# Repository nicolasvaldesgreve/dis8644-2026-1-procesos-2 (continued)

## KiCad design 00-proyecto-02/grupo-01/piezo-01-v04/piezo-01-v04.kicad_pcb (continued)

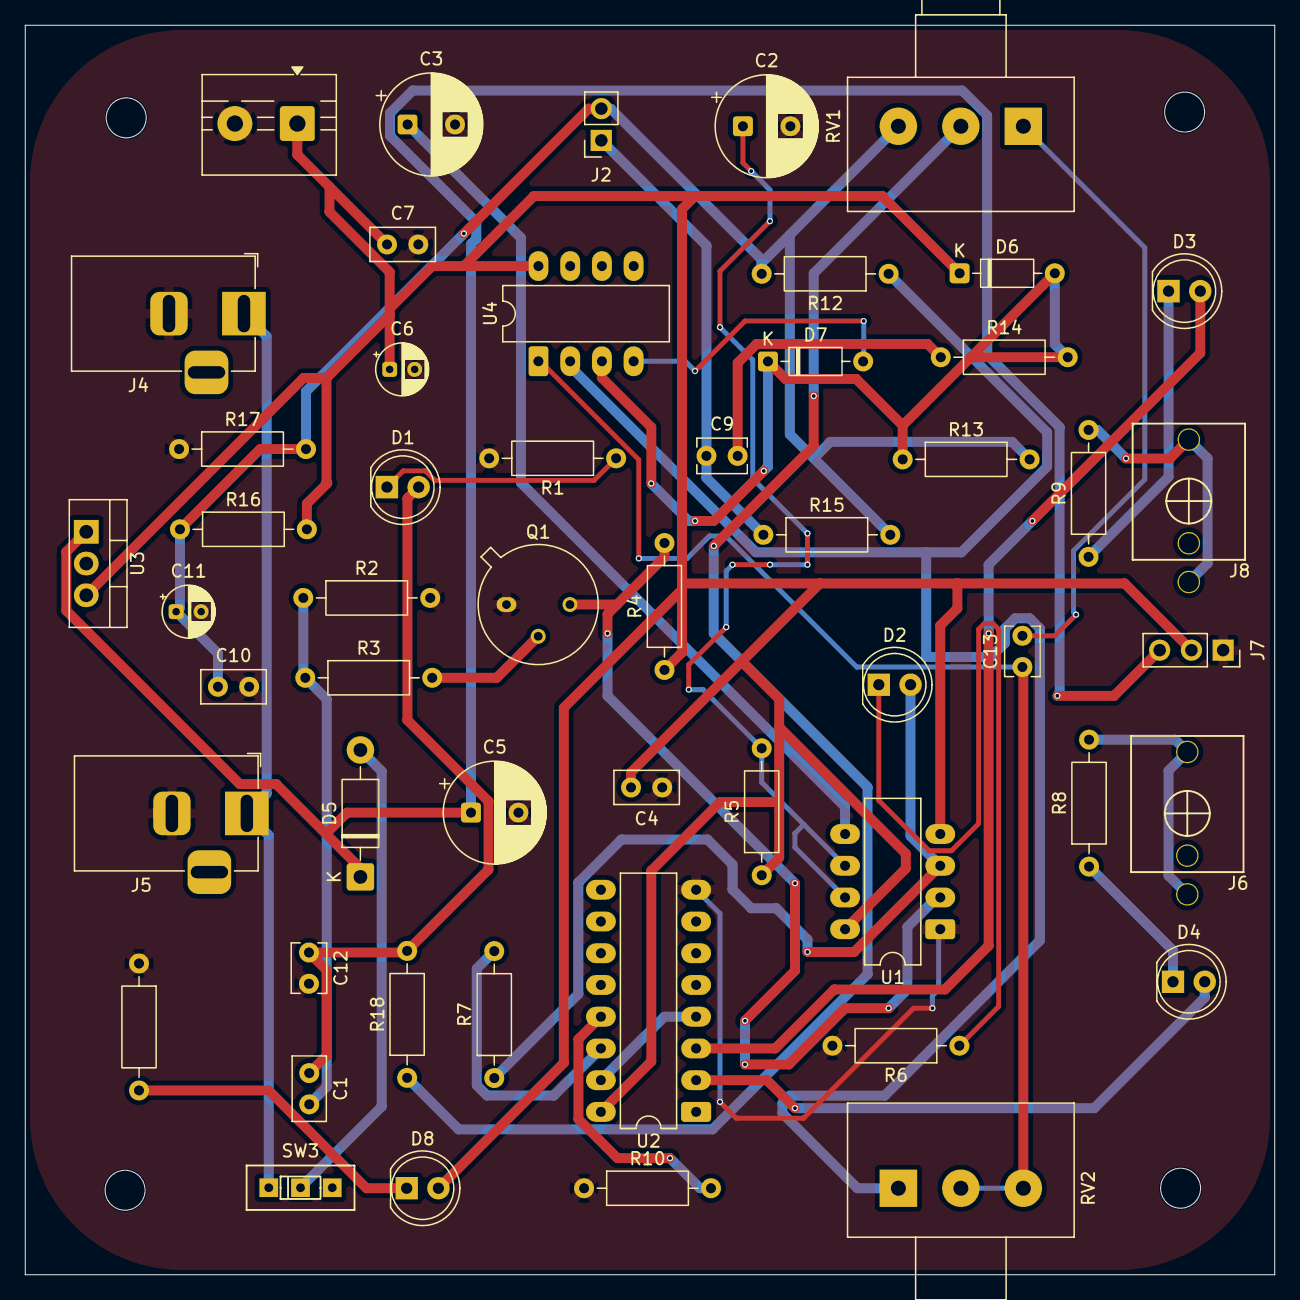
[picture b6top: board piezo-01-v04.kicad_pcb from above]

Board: 2 copper layers, 100.0 x 100.0 mm, 57 parts (0 on the bottom side), 33 nets.

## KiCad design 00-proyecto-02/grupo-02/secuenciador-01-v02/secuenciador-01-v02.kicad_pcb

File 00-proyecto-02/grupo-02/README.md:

# proyecto-02

## Grupo

Número de grupo: 02

Tema del grupo: Secuenciador 

Integrantes:

- Isidora Alvarez / isidoraalvarez
- Dayana Pañitrur / dayanapanitrur
- Camila Ramirez / Estrabismx
- Angel Sabogal / angel-udp
- Tomas Catrileo / tomascatri
  
## Circuito 1 v01: Contador binario - CD4040

### Descripción general/conceptual 1

¿Qué hace el circuito? Intentar explicarlo para gente que no sabe electrónica. Ejemplo: escucha los impactos sobre sí mismo y lo convierte en señales de aviso para otras cosas

Este circuito se categoriza como un secuenciador, es decir que genera corrientes eléctricas en un patrón repetitivo y ordenado. Un ejemplo de esto es un semáforo, ya que se va a prender siempre en el mismo orden:

_VERDE > AMARILLO > ROJO > VERDE > AMARILLO > ROJO > ..._

<br>

### Descripción de funcionamiento 1

Preguntas orientadoras: ¿Qué inputs recibe? ¿Qué outputs entrega? ¿Cómo administra los flujos de inputs a outputs internamente? ¿Qué componente es el "corazón/cerebro"? ¿Qué truco descubrimos en el camino? ¿Especulativamente, qué se podría conectar a este módulo en el futuro?

<br>

Ya definimos que este sistema es un secuenciador, pero algo importante es como está configurada la duración de cada _activación_. Tal como en los semáforos no todos los colores duran lo mismo, en este circuito cada _señal_ tiene una duración única. ¿A que se refiere "duración unica"? En que cada _señal_ está asociada a un número, desde el 0 al 12 y mientras menor sea el número asociado, más rapido se va a _activar_. A continuación se puede observar una representación de este patrón

<br>

Esta es una secuencia binaria y de las cosas más notorias es que cada _canal_ tiene la misma duración prendido y apagado, es decir, el Q3 funciona con 4 _señales apagadas_ y 4 _señales prendidas_. Otro punto interesante es como esta duración tambien sigue un patrón

| Canal / Step | Duración   |
| ------------ | ---------- |
| Q1           | 1 tiempo   |
| Q2           | 2 tiempos  |
| Q3           | 4 tiempos  |
| Q4           | 8 tiempos  |
| Q5           | 16 tiempos |

<br>

Ahora que entendemos como funciona su secuencia, vamos a profundizar más en como este circuito logra generar este proceso. Anteriormente se mencionó (y tmabien se ejemplificó en la imagen) que en cada _"tiempo"_ se van _activando_ las señales correspondientes, estos "_tiempos_" son corrientes eléctricas, es decir, que se necesita una señal intermitente y constante para activar el proceso de conteo. Esto es conocido como **reloj** o **clock**, entonces la velocidad con la que alterne este circuito afectará en como nuestro secuenciador realice su conteo.

Para una mayor compresión se utilizará la siguiente analogía: Tenemos una especie de corazón (Reloj) que cada vez que late (emitir un pulso eléctrico) un semáforo prende sus luces (se activan las salidas del secuenciador)

### Esquemático 

```markdown

```

### PCB 1

```markdown

```

```markdown

```

### Documentación audiovisual funcionamiento protoboard 1

Incluir enlace a video en youtube (puede estar en Oculto) con protoboard funcionando

## Circuito 2

Título módulo 2

### Descripción general/conceptual 2

¿Qué hace el circuito? Intentar explicarlo para gente que no sabe electrónica. Ejemplo: escucha los impactos sobre sí mismo y lo convierte en señales de aviso para otras cosas

### Descripción de funcionamiento 2

Preguntas orientadoras: ¿Qué inputs recibe? ¿Qué outputs entrega? ¿Cómo administra los flujos de inputs a outputs internamente? ¿Qué componente es el "corazón/cerebro"? ¿Qué truco descubrimos en el camino? ¿Especulativamente, qué se podría conectar a este módulo en el futuro?

### Esquemático 2

```markdown

```

### PCB 2

```markdown

```

```markdown

```

### Documentación audiovisual funcionamiento protoboard 2

Incluir enlace a video en youtube (puede estar en Oculto) con protoboard funcionando

## Otros circuitos

¿Usaron otro circuito temporal para activar algunas cosas? ¿para probar inputs-outputs? Detallar cuales

## Colaboración con otros grupos

### ¿Cómo ayudé a otro grupo?

Lorem ipsum

### ¿Cómo me ayudó otro grupo?

lorem ipsum

## Bibliografía

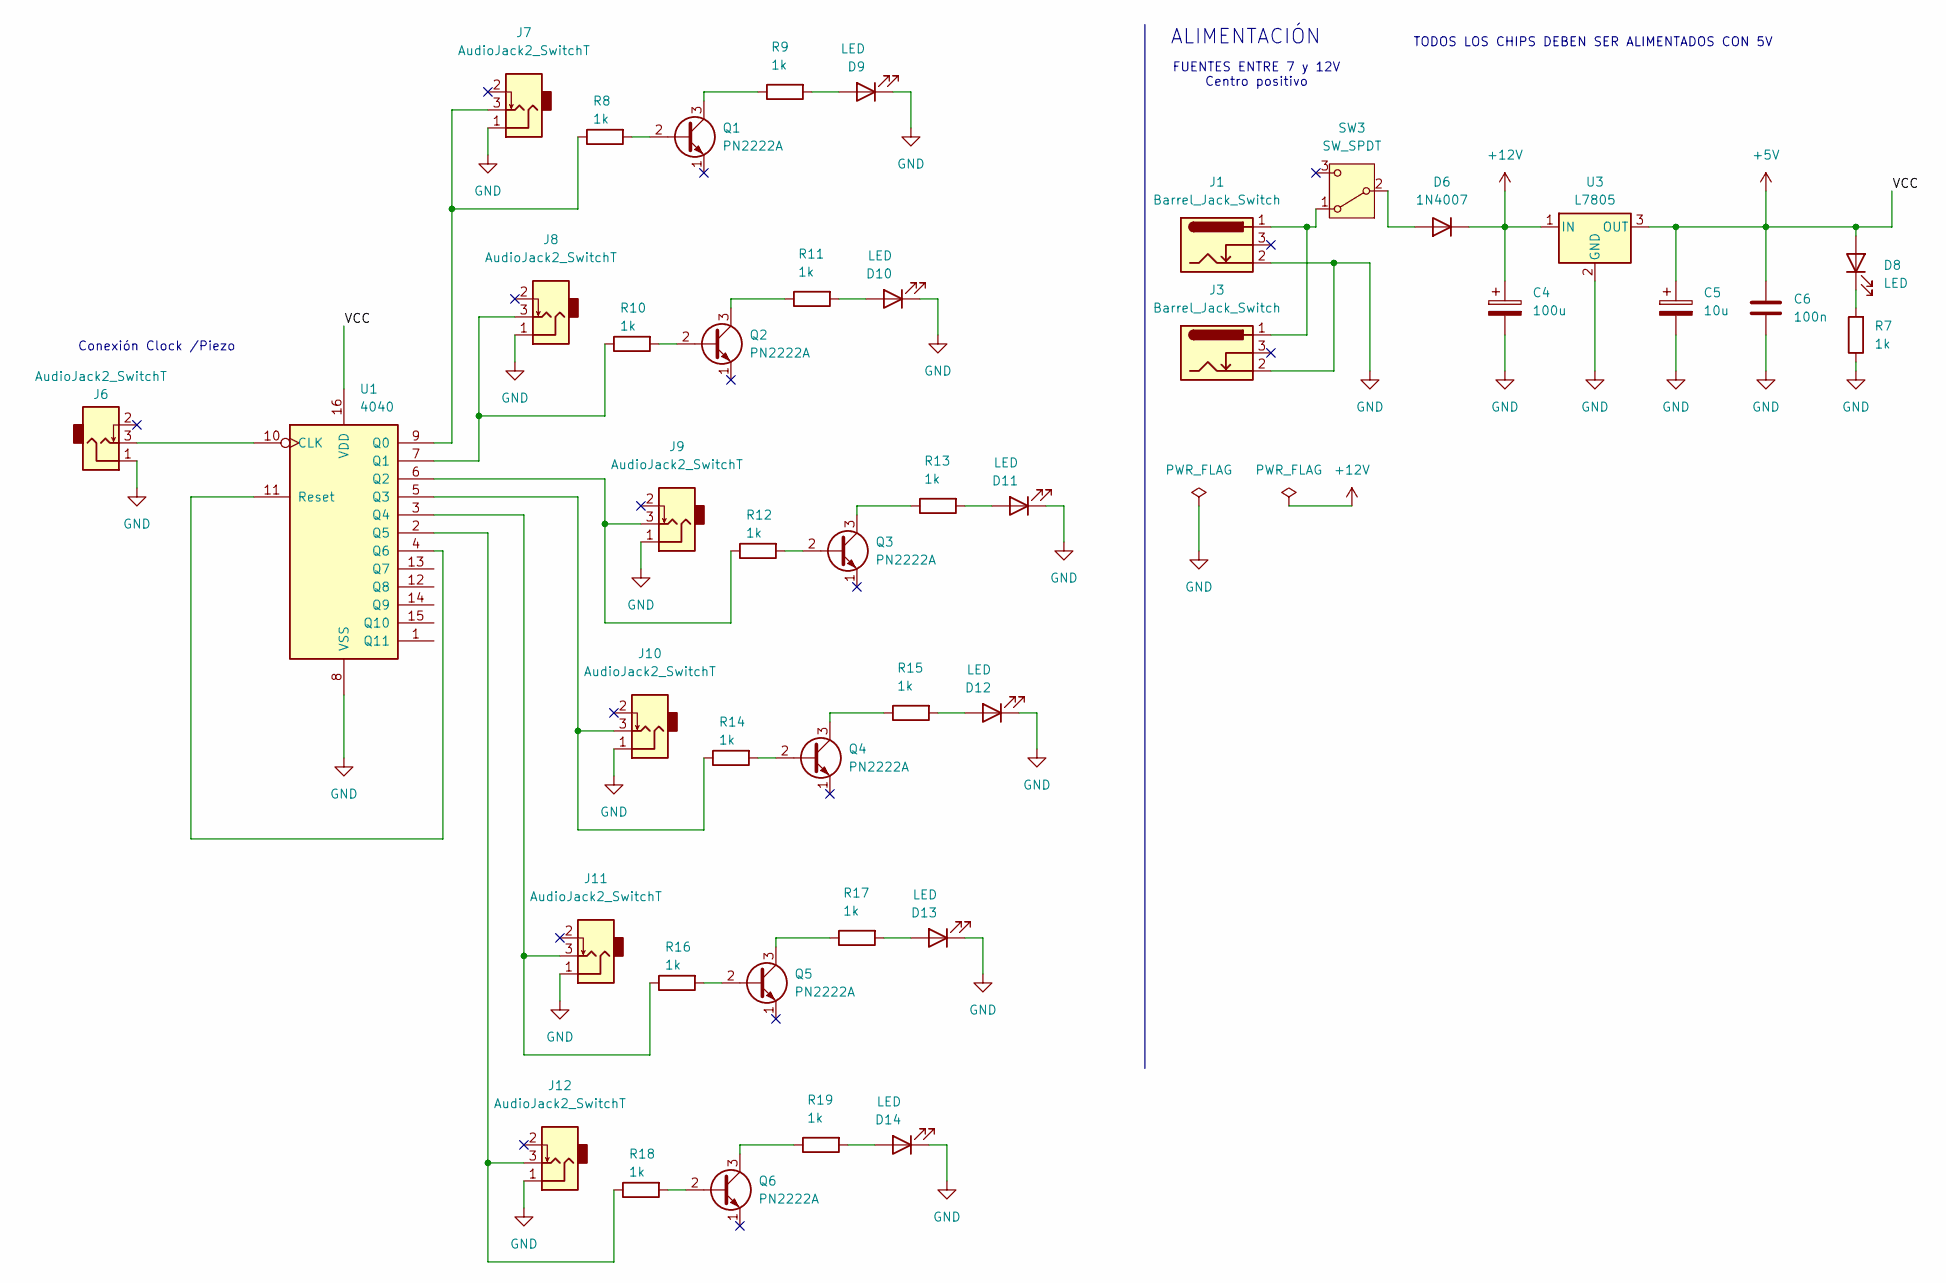
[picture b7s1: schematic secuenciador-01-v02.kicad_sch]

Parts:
C4: 100u; CP_Radial_D8.0mm_P3.80mm
C5: 10u; CP_Radial_D4.0mm_P2.00mm
C6: 100n; C_Disc_D5.0mm_W2.5mm_P2.50mm
D6: 1N4007; D_DO-41_SOD81_P10.16mm_Horizontal
D8, D9, D10, D11, D12, D13, D14: LED; LED_D5.0mm
J1, J3: Barrel_Jack_Switch; BarrelJack_Horizontal
J6, J7, J8, J9, J10, J11, J12: AudioJack2_SwitchT; PJ301M-12
Q1, Q2, Q3, Q4, Q5, Q6: PN2222A; TO-92_Inline
R7, R8, R9, R10, R11, R12, R13, R14, R15, R16, R17, R18, R19: 1k; R_Axial_DIN0207_L6.3mm_D2.5mm_P10.16mm_Horizontal
SW3: SW_SPDT; spdt_ssd12d00g3
U1: 4040; DIP-16_W7.62mm
U3: L7805; TO-220-3_Horizontal_TabDown

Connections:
+5V: C5.1, C6.1, D8.2 (A), U1.16 (VDD), U3.3 (OUT)
+12V: C4.1, D6.1 (K), U3.1 (IN)
GND: C4.2, C5.2, C6.2, D9.1 (K), D10.1 (K), D11.1 (K), D12.1 (K), D13.1 (K), D14.1 (K), J1.2, J3.2, J6.1, J7.1, J8.1, J9.1, J10.1, J11.1, J12.1, R7.1, U1.8 (VSS), U3.2 (GND)
unnamed: D6.2 (A), SW3.2 (B)
unnamed: D8.1 (K), R7.2
unnamed: D9.2 (A), R9.2
unnamed: D10.2 (A), R11.2
unnamed: D11.2 (A), R13.2
unnamed: D12.2 (A), R15.2
unnamed: D13.2 (A), R17.2
unnamed: D14.2 (A), R19.2
unnamed: Q1.2 (B), R8.2
unnamed: Q1.3 (C), R9.1
unnamed: Q2.2 (B), R10.2
unnamed: Q2.3 (C), R11.1
unnamed: Q3.2 (B), R12.2
unnamed: Q3.3 (C), R13.1
unnamed: Q4.2 (B), R14.2
unnamed: Q4.3 (C), R15.1
unnamed: Q5.2 (B), R16.2
unnamed: Q5.3 (C), R17.1
unnamed: Q6.2 (B), R18.2
unnamed: Q6.3 (C), R19.1
unnamed: J1.1, J3.1, SW3.1 (A)
unnamed: J6.3, U1.10 (CLK)
unnamed: J7.3, R8.1, U1.9 (Q0)
unnamed: J8.3, R10.1, U1.7 (Q1)
unnamed: J9.3, R12.1, U1.6 (Q2)
unnamed: J10.3, R14.1, U1.5 (Q3)
unnamed: J11.3, R16.1, U1.3 (Q4)
unnamed: J12.3, R18.1, U1.2 (Q5)
unnamed: U1.4 (Q6), U1.11 (Reset)

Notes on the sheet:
Conexión Clock /Piezo
ALIMENTACIÓN
FUENTES ENTRE 7 y 12V Centro positivo
TODOS LOS CHIPS DEBEN SER ALIMENTADOS CON 5V

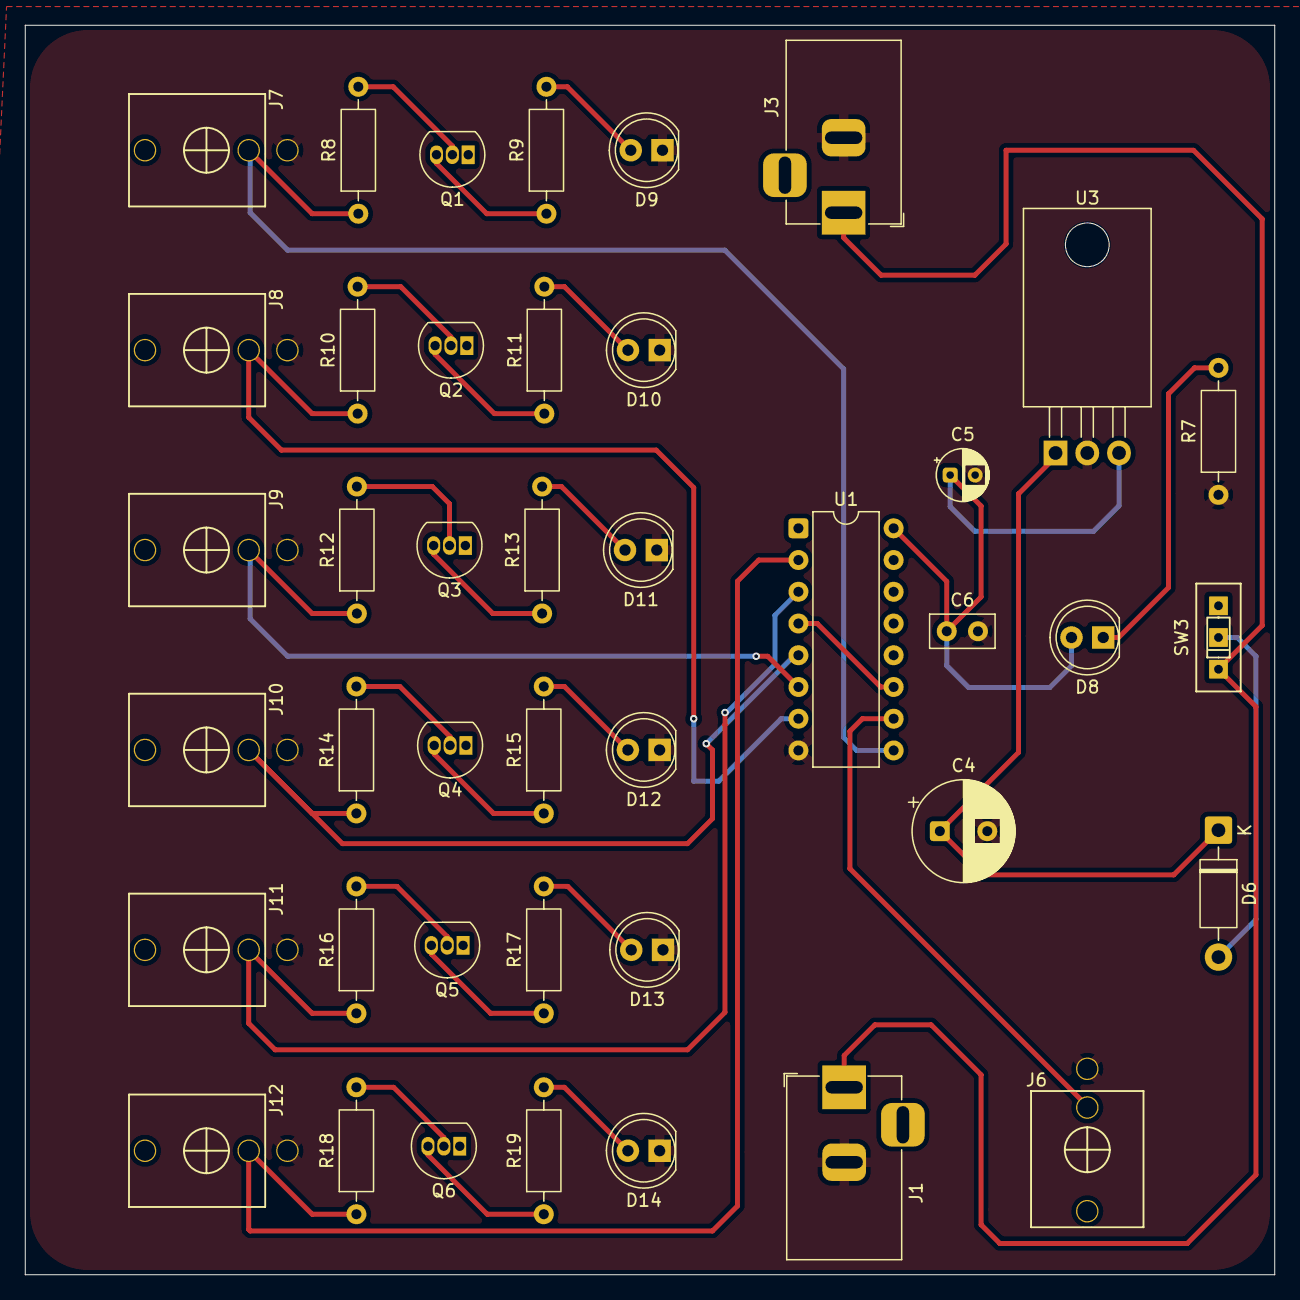
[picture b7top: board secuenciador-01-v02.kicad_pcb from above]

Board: 2 copper layers, 100.0 x 100.0 mm, 42 parts (0 on the bottom side), 32 nets.

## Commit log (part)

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2026-05-15 Update README with note on recess week
    Added a note about the week of recess with no classes.
2026-05-15 Update README.md with KiCad installation and project notes
    Added notes and workflow steps for KiCad usage in the README.
2026-05-19 Apuntes charlas
    Corrected the description of the Simon scanner's measurements regarding trees and mountains.
2026-05-22 arreglo redacción
2026-05-22 Update README
    Added initial information about the 4040 chip and its functionality.
2026-05-22 sesion-in-correcta
2026-05-23 fotos kicad
2026-05-24 Add date to README for sesion-10b
2026-05-24 Add date to sesion-12b README
2026-05-25 agrego imagen taiko
2026-05-26 investigación pt.2
2026-05-26 Rename avance2.PNG to avance2.png
2026-05-26 crear carpeta v02
2026-05-27 agregar
2026-05-28 Rename Chip 4015.jpg to Chip4015.jpg
2026-05-29 agrego opinión libro
2026-05-29 Enhance README with TS connector and circuit details
    Added detailed information about TS connectors, barrel switches, and circuit recreations, along with images.
2026-05-31 agrego estandar clase
2026-06-02 Update README for session 10a with new content
2026-06-03 cambiar-carpeta
2026-06-03 Update group number and team members in README
    Updated group number and added member names with GitHub links.
2026-06-03 mover lib/
2026-06-03 agregar v03
2026-06-03 cambiar v1 por v01
2026-06-04 crear carpeta
2026-06-04 agrego
2026-06-04 agrego info 02
2026-06-05 Create borrar
2026-06-05 desarrollo-proyecto02.md
2026-06-05 Rename chirigue.jpg to chirihue.jpg
2026-06-05 Document circuit connections in README
    Added detailed circuit connections and descriptions for CD4046, TL072, LM386, and potentiometers in the README.
2026-06-05 listo-final-real-hola
2026-06-05 Update README with session notes and issues
    Added detailed notes about the session activities and issues encountered with piezo-02, including images and concepts discussed.
2026-06-05 pcb-nuevas
2026-06-06 añadida g01-secu01
2026-06-06 agregar mas apuntes
2026-06-06 agregar guion faltante
2026-06-06 agregar mas apuntes grupo 04
2026-06-09 agrego apuntes
2026-06-09 partitura-test
2026-06-12 Update README
    Added notes on session topics including technology and PCB manufacturing.
2026-06-15 Rename 28429041388423805.jpg to idea-05.jpg
2026-06-16 agrego imagenes
2026-06-16 aun en edicion
2026-06-17 avance-pre-examen
2026-06-17 Apuntes-13b
2026-06-19 color-tamaño-correcto
2026-06-21 Revise README for sesion-14a with class updates
    Updated the README with corrections and additional details about the soldering class process and post-class reflections.
2026-06-23 sesion 13b
2026-06-28 hola-estas-son-imagenes
2026-06-28 ahora-si-hola
2026-06-30 Update README.md with team member links
2026-06-30 Update README with team and BOM details
    Added team members and detailed BOM for various components including oscillators and percussion instruments.
